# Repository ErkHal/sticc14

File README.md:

# Sticc14
3x5 Mechanical macropad PCB. Fully open-source.

## Specs

* 14 keys
* Throughhole/SMD diodes
* QMK Compatible
* Uses Pro Micro (Atmega32u4)

## Firmware
- Uses QMK: https://qmk.fm/  
- Sticc14 repository: https://github.com/qmk/qmk_firmware/tree/master/keyboards/handwired/sticc14

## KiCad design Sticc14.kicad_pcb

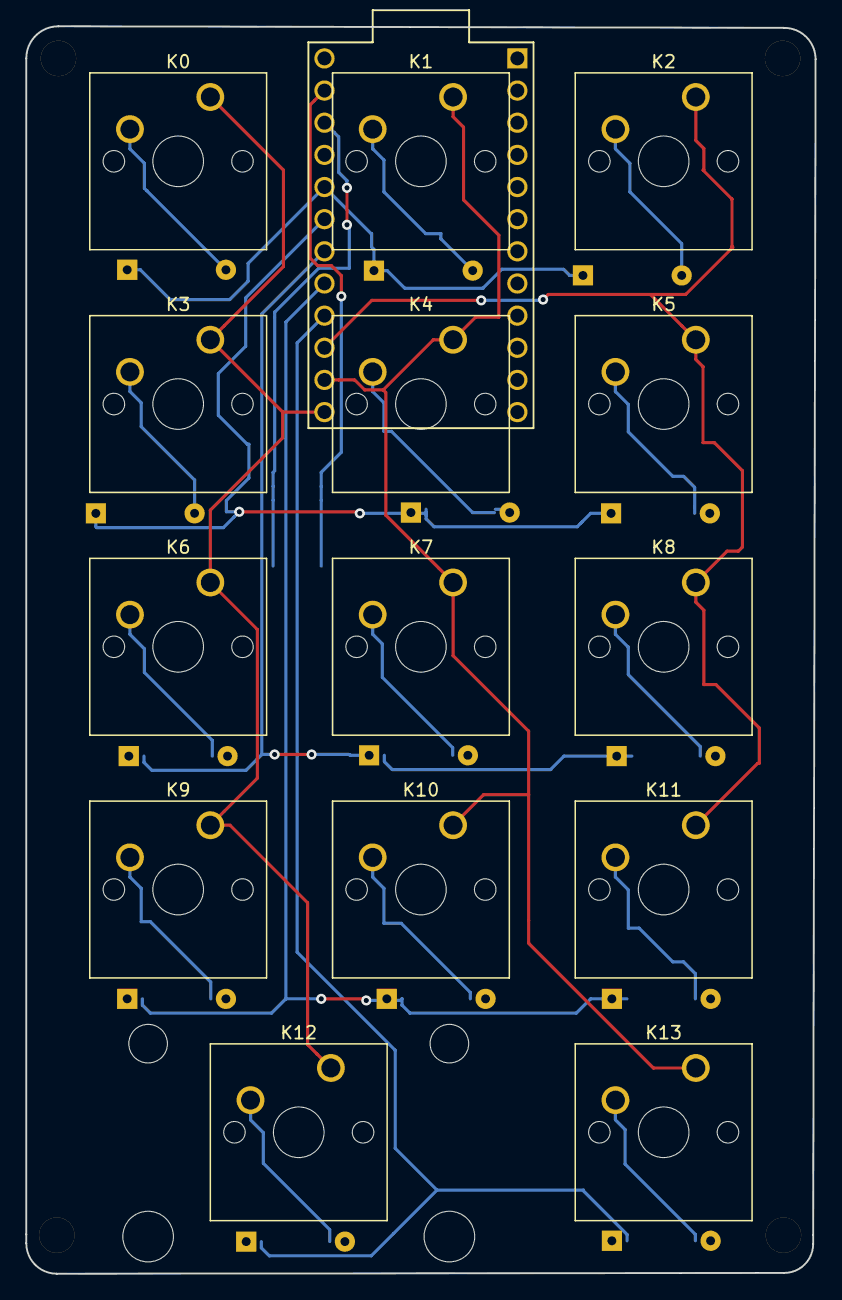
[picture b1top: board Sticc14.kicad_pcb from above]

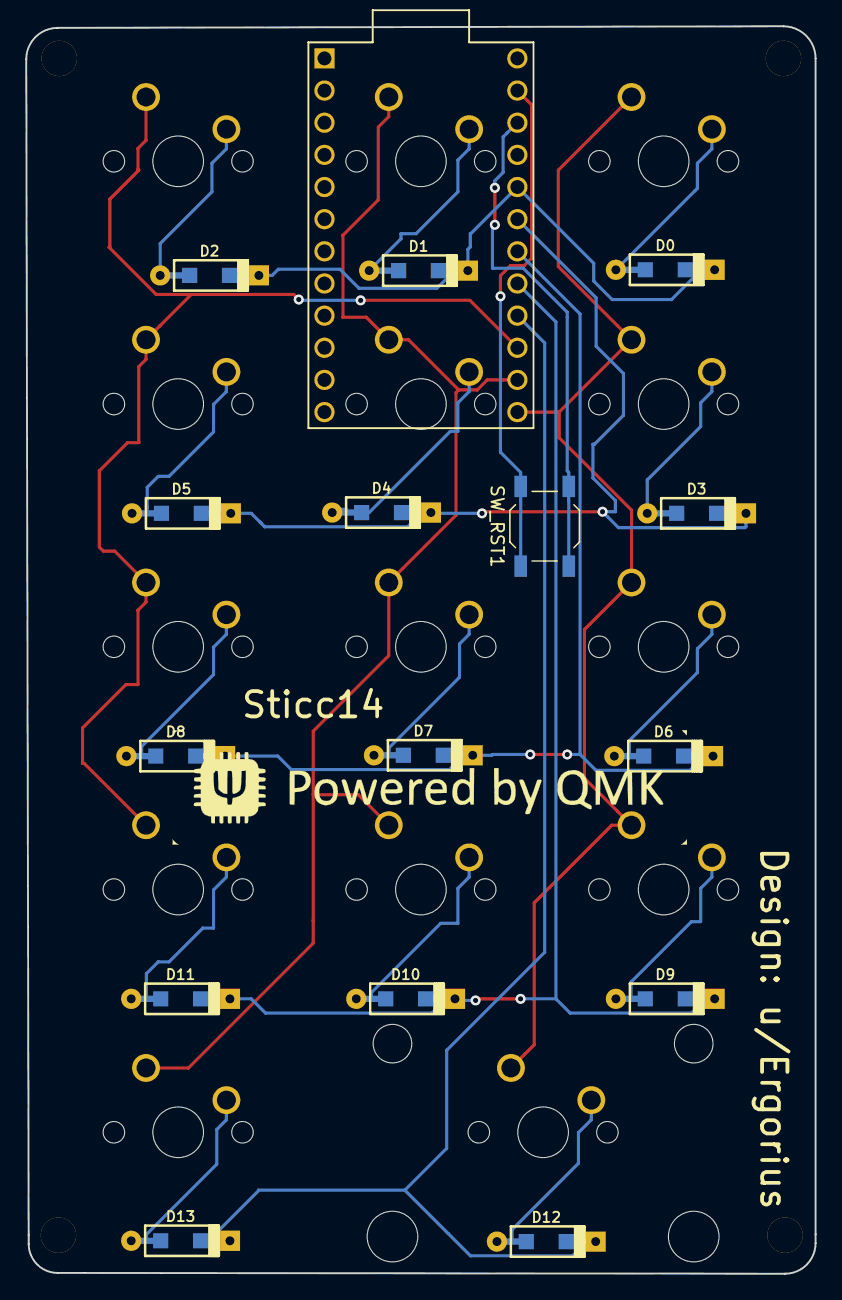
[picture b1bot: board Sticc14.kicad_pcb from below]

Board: 2 copper layers, 62.4 x 98.6 mm, 34 parts (16 on the bottom side), 24 nets.

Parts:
D0, D1, D2, D3, D4, D5, D6, D7, D8, D9, D10, D11, D12, D13: D; D_SOD123_axial
HOLE_M2.6, HOLE_M2.6#2, HOLE_M2.6#3, HOLE_M2.6#4: VAL**; HOLE_M2.6
K0, K1, K2, K3, K4, K5, K6, K7, K8, K9, K10, K11, K13: KEYSW; SW_Cherry_MX1A_1.00u_PCB
K12: KEYSW; SW_Cherry_MX1A_2.00u_PCB
SW_RST1: SW_PUSH; SW_SPST_TL3342
U1: ProMicro

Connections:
Col0: K0.1, K3.1, K6.1, K9.1, K12.1, U1.13
Col1: K1.1, K4.1, K7.1, K10.1, K13.1, U1.14
Col2: K2.1, K5.1, K8.1, K11.1, U1.15
unnamed: D0.2, K0.2
unnamed: D1.2, K1.2
unnamed: D2.2, K2.2
unnamed: D3.2, K3.2
unnamed: D4.2, K4.2
unnamed: D5.2, K5.2
unnamed: D6.2, K6.2
unnamed: D7.2, K7.2
unnamed: D8.2, K8.2
unnamed: D9.2, K9.2
unnamed: D10.2, K10.2
unnamed: D11.2, K11.2
unnamed: D12.2, K12.2
unnamed: D13.2, K13.2
unnamed: SW_RST1.1, U1.23
unnamed: SW_RST1.2, U1.22
Row0: D0.1, D1.1, D2.1, U1.20
Row1: D3.1, D4.1, D5.1, U1.19
Row2: D6.1, D7.1, D8.1, U1.18
Row3: D9.1, D10.1, D11.1, U1.17
Row4: D12.1, D13.1, U1.16

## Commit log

2020-02-06 Add DXF Files for case designs
